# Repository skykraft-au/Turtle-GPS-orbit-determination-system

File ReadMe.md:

# Overview
The Turtle GPS is an open-source, cost-effective, low-power, and low-weight solution to orbit determination. The device resolves the issues faced by standard tracking methods such as radar while democratising space by making tracking cooperative and community-based. The device satisfies CoCom regulations by being post-processed and non-continuous; instead, it beacons GPS data over LoRa packets at specified intervals.

The device is highly configurable through the FPGA Verilog code; see the configuration section below for more information.

Further development on the device is needed; the community is welcome to contribute to this. Information on directions for this development can be found in the Todo section below.

[!WARNING] Turtle GPS v2.0 contains known hardware issues in the flash programming and power supply circuitry which prevent correct operation in the default configuration. These issues are corrected in Turtle GPS v2.1. See GPS v2.0/KNOWN_ISSUES.md for more information. 

# Usage of the Device
## QuickStart Guide for Testing
Once the PCB is fully assembled, the HF MMCX line can be connected to a passive or active GPS antenna. If it is active, in the case of v2.1, the onboard bias tee can power it, otherwise an external bias tee is required. The Turtle GPS should be connected to a 3.3 V power supply, either a small solar panel, a benchtop power supply, or a Lithium-Ion battery. The output can either be connected to an antenna which transmits to a LoRa receiver or directly connected to the receiver with a coaxial cable and a 3 dB attenuator. The LoRa receiver could be setup with a module like the SX1278 RA-02, connected to a microcontroller configured to receive the data packets.

If the Flash has not been programmed, the JTAG header should be connected to a computer over a digilent JTAG-HS3 programming cable or similar. Then, Vivado should be used to compile a bitstream in the relevant project found in this repository. A memory config file using QSPI should be created in Vivado, from this bitstream before being used to write the Flash memory over the JTAG, again with Vivado.

Once programmed, upon being powered the Turtle GPS will begin receiving and transmitting packets of data, following a pseudo-random delay for the first cycle. This delay was implemented to prevent continuous transmission on a tumbling satellite. The packets received over LoRa should be processed with a computer as they are essentially just IQ data from the GPS signal, not processed position or time data.

## Configuration of the Device
By default, the packets transmitted over LoRa are 512 bits wide and include a unique, user-defined satellite ID Code, packet index, user-defined bits, and the actual data.
| Number of Bits | Bit Locations | Purpose |
| -------------- | ------------- | ------- |
| 24 | \[511:488\] | Satellite ID Code |
| 12 | \[487:476\] | Packet Index |
| 28 | \[475:448\] | User-defined bits |
| 448 | \[447:0\] | GPS IQ Data |

The user-defined bits can be configured by changing the value of the respective register in the Verilog code. The configuration of the MAX2771 GNSS Receiver and the LoRa SX1276 can be changed by adjusting the values of their respective configuration registers in the MAX_Driver and LORA_Driver Verilog modules, respectively.

The total transmission size, as well as the sample size and whether samples are continuous or not, can all be configured through the value of the GPS_Config register in the GPS_Top Verilog module. Comments are included in the code to assist users with this.

# Changelog
## Most Recent Version (Turtle GPS v2.1)
- Fixes including 10 kOhm pull-up resistors on Flash Pins, lowered pull up resistance to 1 kOhm on mode pin pullup to prevent metastable behaviour on boot, boost converter swapped to MAX8575, done pin pulled up instead of down, and swapped the power supply diode to B130-13-F for higher current capability.
- Swapped LDOs in the power supply for availability, and lower supply noise.
- Made MMCX connectors side mounted instead of front mounted.
- Swapped power header for the M80-8420245 side-mounted Harwin connector.
- Added an L1 SAW Filter to the RF path around the MAX2771 digitiser.
- Updated LoRa RF path to handle frequencies between 400 and 440 MHz.
- Added a 3.3 V Bias Tee to the GNSS RF input path to allow for an active antenna to be directly connected.
- Moved bulk capacitors to the front of the board allowing direct mounting of the PCB to a satellite chassis with a thin (~0.3 mm) thermally conductive layer.
- Changed Flash to S25FL128LAGMFI010 due to part availability.
- Changed LoRa TCXO to TX21-M010S-32.000-X-R due to part avilability.
- Organised KiCAD Schematic into five distinct sections and added 3D models to components.
- Swapped LoRa clock enable voltage divider for a single pull-up resistor.
- Added voltage divider to the relay in the RF path to better match datasheet requirements.
- Reworked trace length matching for the JTAG, and the Flash memory.
- Updated version number and date.

## Note regarding the Turtle GPS v2.0
The Turtle GPS v2.0 does not work by default, as there are issues regarding the flash and power supply components on the board; these issues are resolved in version 2.1.

# Todo
- Update code to default the LoRa frequency to 401 MHz to 403 MHz and cascade the FIR (or implement a CIC) to allow for a sharper cutoff to be attained with the limited FPGA resources.
- Program LoRa receiving capabilities into the FPGA to allow for remote shutdown with a unique user-defined code.
- Optimise size, weight, and performance of the device
- Test in orbit
- Set up a public website for uploading and processing of data
- Add satellite ID code generator and logger to the website

# Licensing

This repository contains material under multiple licenses.

The Turtle GPS was conceived of by Craig Benson and implemented by Dino Colling as part of work conducted for, and licenced by, Skykraft Pty Ltd.

Copyright © Skykraft Pty Ltd. All rights are licensed as described below.

## Hardware

The hardware design files are licensed under CERN-OHL-P v2.

This includes:
- GPS v2.0/KiCad PCB/
- GPS v2.1/KiCad PCB/

## HDL and Software

The HDL and software source code are licensed under the MIT License.

This includes:
- GPS v2.0/Software and HDL/
- GPS v2.1/Software and HDL/

## Documentation

Documentation, diagrams, and images are licensed under
Creative Commons Attribution 4.0 International (CC BY 4.0).

This includes:
- GPS v2.0/BoM/
- GPS v2.1/BoM/

A copy of each license is available in the licenses/ directory.

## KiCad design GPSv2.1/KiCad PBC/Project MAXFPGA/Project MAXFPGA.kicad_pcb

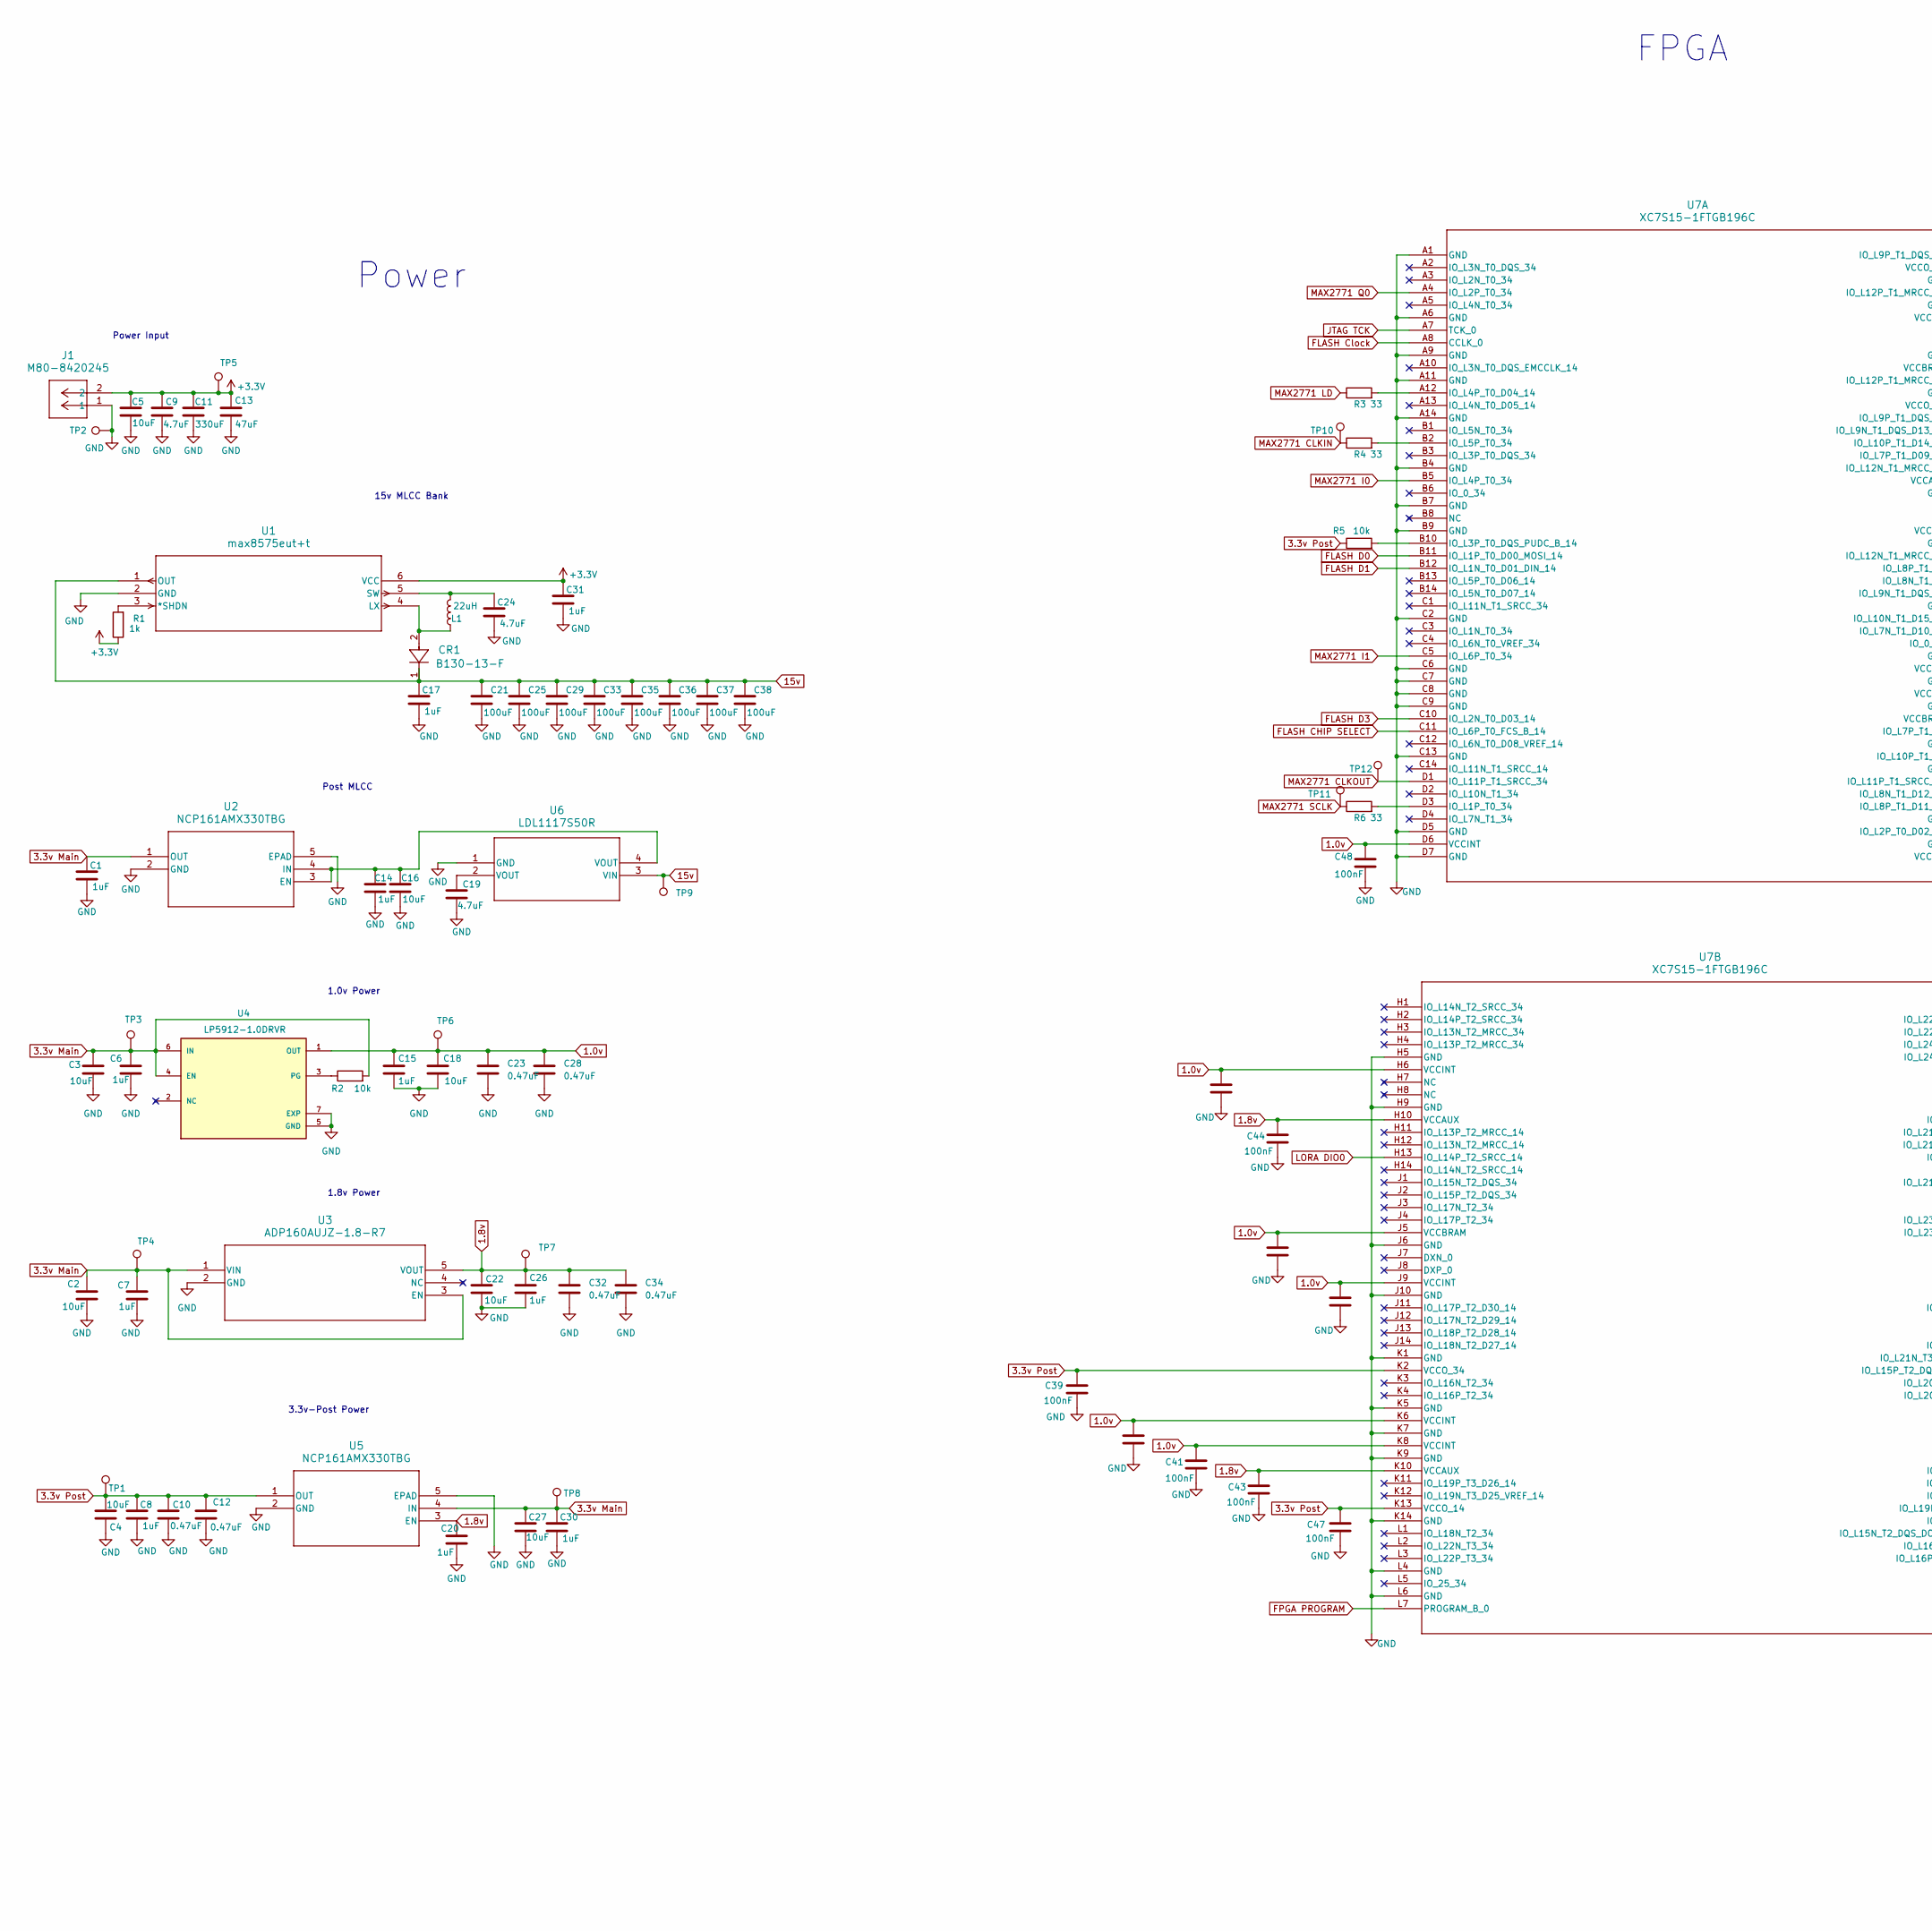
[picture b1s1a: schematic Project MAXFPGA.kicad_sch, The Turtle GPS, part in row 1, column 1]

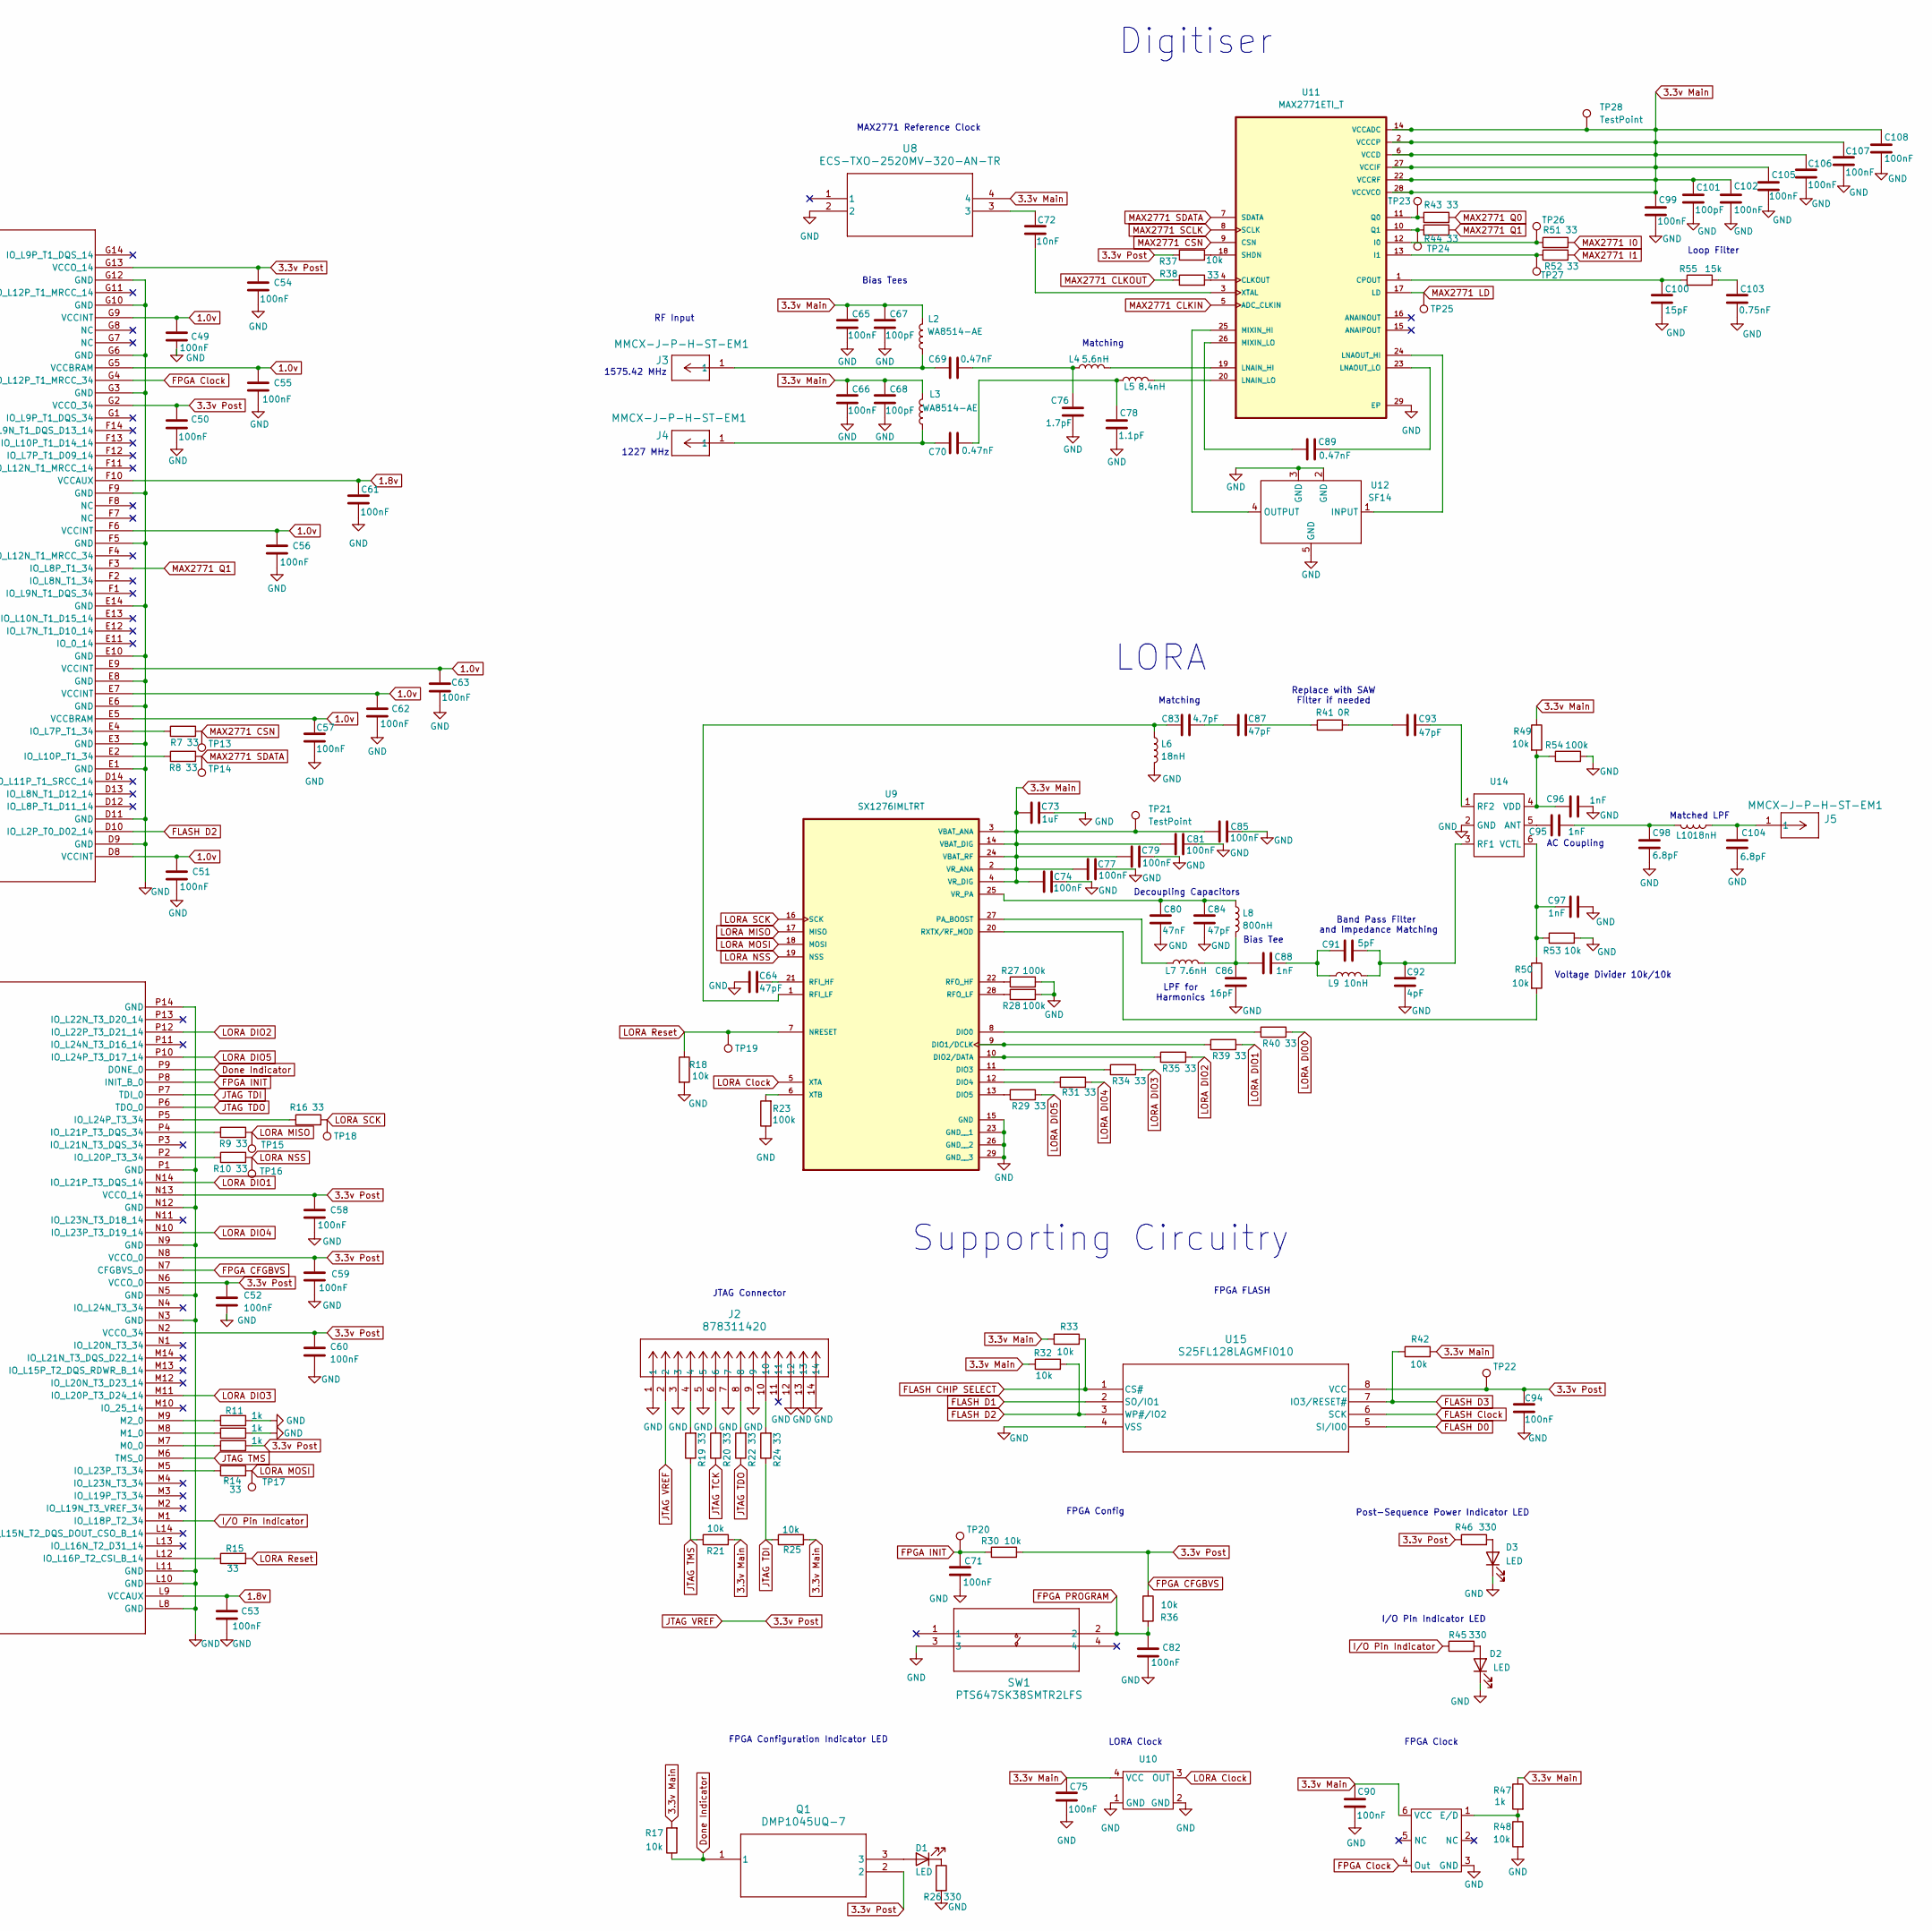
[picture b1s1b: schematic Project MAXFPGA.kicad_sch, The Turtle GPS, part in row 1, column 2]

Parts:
C1, C6, C7, C8, C14, C15, C17, C20, C26, C30, C31, C73: 1uF; C_0402_1005Metric
C2, C3, C4, C5, C16, C18, C22, C27: 10uF; C_0402_1005Metric
C9, C19: 4.7uF; C_0402_1005Metric
C10, C12, C23, C28, C32, C34: 0.47uF; C_0402_1005Metric
C11: 330uF; C_1210_3225Metric
C13: 47uF; C_1206_3216Metric
C21, C25, C29, C33, C35, C36, C37, C38: 100uF; C_1210_3225Metric
C24: 4.7uF; C_0603_1608Metric
C39, C40, C41, C42, C43, C44, C45, C46, C47, C48, C49, C50, C51, C52, C53, C54, C55, C56, C57, C58, C59, C60, C61, C62, C63, C71, C82: 100nF; CAPC0603X33N
C64, C84, C87, C93: 47pF; C_0402_1005Metric
C65, C66, C74, C75, C77, C79, C81, C85, C90, C94, C99, C102, C105, C106, C107, C108: 100nF; C_0402_1005Metric
C67, C68, C101: 100pF; C_0402_1005Metric
C69, C70, C89: 0.47nF; C_0201_0603Metric
C72: 10nF; C_0402_1005Metric
C76: 1.7pF; C_0402_1005Metric
C78: 1.1pF; C_0402_1005Metric
C80: 47nF; C_0402_1005Metric
C83: 4.7pF; C_0402_1005Metric
C86: 16pF; C_0402_1005Metric
C88, C95: 1nF; C_0201_0603Metric
C91: 5pF; C_0402_1005Metric
C92: 4pF; C_0402_1005Metric
C96, C97: 1nF; C_0402_1005Metric
C98, C104: 6.8pF; C_0402_1005Metric
C100: 15pF; CAPC17595_87N_KEM
C103: 0.75nF; C_0402_1005Metric
CR1: B130-13-F; D_SMA
D1, D2, D3: LED; LED_SML-D12U1WT86
J1: M80-8420245; CONN_M80-84202_HRW
J2: 878311420; JTAG_Conn
J3, J4, J5: MMCX-J-P-H-ST-EM1; CONN_MMCX-J-P-H-ST-EM1_SAI
L1: 22uH; L_0805_2012Metric
L2, L3: WA8514-AE; RF_Choke
L4: 5.6nH; INDC1006X60N
L5: 8.4nH; INDC1006X60N
L6, L10: 18nH; INDC1006X60N
L7: 7.6nH; INDC1006X60N
L8: 800nH; INDC1006X60N
L9: 10nH; INDC1006X60N
Q1: DMP1045UQ-7; DONE_FET
R1, R11, R12, R13, R47: 1k; RESC1005X40N
R2, R5, R17, R18, R21, R25, R30, R32, R33, R36, R37, R42, R48, R49, R50, R53: 10k; RESC1005X40N
R3, R4, R6, R7, R8, R9, R10, R14, R15, R16, R19, R20, R22, R24, R29, R31, R34, R35, R38, R39, R40, R43, R44, R51, R52: 33; RESC1005X40N
R23, R27, R28, R54: 100k; RESC1005X40N
R26, R45, R46: 330; RESC1005X40N
R41: 0R; RESC1005X40N
R55: 15k; RES_ERA2AEB153X
SW1: PTS647SK38SMTR2LFS; PTS647SK38SMTR2LFS_CNK
TP1, TP2, TP3, TP4, TP5, TP6, TP7, TP8, TP9, TP10, TP11, TP12, TP13, TP14, TP15, TP16, TP17, TP18, TP19, TP20, TP21, TP22, TP23, TP24, TP25, TP26, TP27, TP28: TestPoint; TestPoint_Pad_1.0x1.0mm
U1: max8575eut+t; Boost
U2, U5: NCP161AMX330TBG; XDFN4_711AJ_ONS_OSI
U3: ADP160AUJZ-1.8-R7; 1.8V_REG
U4: LP5912-1.0DRVR; SON65P200X200X80-7N; PARTREV D
U6: LDL1117S50R; SOT223_STM-M
U7: XC7S15-1FTGB196C; FTGB196_AMD
U8: ECS-TXO-2520MV-320-AN-TR; SMD04_XTAL_2P5X2_ECS
U9: SX1276IMLTRT; QFN65P600X600X100-29N; PARTREV 5
U10: LoRa_Clock_32MHz
U11: MAX2771ETI_T; QFN50P500X500X80-29N
U12: SF14; Untitled
U13: FPGA_Clock_100MHz
U14: ASWD-S2-000
U15: S25FL128LAGMFI010; SOIC8_S25FL_CYP-M

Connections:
1.0v: C15.1, C18.1, C23.1, C28.1, C40.1, C41.1, C42.1, C45.1, C46.1, C48.2, C49.1, C51.1, C55.1, C56.1, C57.1, C62.1, C63.2, TP6.1 (1_1), U4.1 (OUT), U7.D6 (VCCINT), U7.D8 (VCCINT), U7.E5 (VCCBRAM), U7.E7 (VCCINT), U7.E9 (VCCINT), U7.F6 (VCCINT), U7.G5 (VCCBRAM), U7.G9 (VCCINT), U7.H6 (VCCINT), U7.J5 (VCCBRAM), U7.J9 (VCCINT), U7.K6 (VCCINT), U7.K8 (VCCINT)
1.8v: C20.1, C22.2, C26.2, C32.1, C34.1, C43.2, C44.1, C53.2, C61.2, TP7.1 (1_1), U3.5 (VOUT), U5.3 (EN), U7.F10 (VCCAUX), U7.H10 (VCCAUX), U7.K10 (VCCAUX), U7.L9 (VCCAUX)
3.3v Main: C1.1, C2.1, C3.1, C6.1, C7.1, C27.1, C30.1, C65.2, C66.2, C67.2, C68.2, C73.1, C74.1, C75.1, C77.1, C79.1, C81.1, C85.1, C90.1, C99.1, C101.1, C102.1, C105.1, C106.1, C107.1, C108.1, L2.2, L3.2, R2.2, R17.2, R21.2, R25.2, R32.1, R33.1, R42.2, R47.1, R49.1, TP3.1 (1_1), TP4.1 (1_1), TP8.1 (1_1), TP21.1 (1_1), TP28.1 (1_1), U2.1 (OUT), U3.1 (VIN), U3.3 (EN), U4.4 (EN), U4.6 (IN), U5.4 (IN), U8.4, U9.2 (VR_ANA), U9.3 (VBAT_ANA), U9.4 (VR_DIG), U9.14 (VBAT_DIG), U9.24 (VBAT_RF), U10.4 (VCC), U11.2 (VCCCP), U11.6 (VCCD), U11.14 (VCCADC), U11.22 (VCCRF), U11.27 (VCCIF), U11.28 (VCCVCO), U13.6 (VCC)
3.3v Post: C4.1, C8.1, C10.1, C12.1, C39.1, C47.1, C50.1, C52.1, C54.1, C58.1, C59.1, C60.1, C94.1, J2.2, Q1.2, R5.1, R13.2, R30.2, R36.1, R37.1, R46.1, TP1.1 (1_1), TP22.1 (1_1), U5.1 (OUT), U7.G2 (VCCO_34), U7.G13 (VCCO_14), U7.K2 (VCCO_34), U7.K13 (VCCO_14), U7.N2 (VCCO_34), U7.N6 (VCCO_0), U7.N7 (CFGBVS_0), U7.N8 (VCCO_0), U7.N13 (VCCO_14), U15.8 (VCC); also elsewhere on the board
15v: C17.1, C21.2, C25.2, C29.2, C33.2, C35.2, C36.2, C37.2, C38.2, CR1.1, TP9.1 (1_1), U1.1 (OUT), U6.3 (VIN)
+3.3V: C5.2, C9.2, C11.2, C13.2, C31.1, J1.2, R1.1, TP5.1 (1_1), U1.6 (VCC); also elsewhere on the board
Done Indicator: Q1.1, R17.1, U7.P9 (DONE_0)
FLASH CHIP SELECT: R33.2, U7.C11 (IO_L6P_T0_FCS_B_14), U15.1 (CS#); also elsewhere on the board
FLASH Clock: U7.A8 (CCLK_0), U15.6 (SCK); also elsewhere on the board
FLASH D0: U7.B11 (IO_L1P_T0_D00_MOSI_14), U15.5 (SI/IO0); also elsewhere on the board
FLASH D1: U7.B12 (IO_L1N_T0_D01_DIN_14), U15.2 (SO/IO1); also elsewhere on the board
FLASH D2: R32.2, U7.D10 (IO_L2P_T0_D02_14), U15.3 (WP#/IO2); also elsewhere on the board
FLASH D3: R42.1, U7.C10 (IO_L2N_T0_D03_14), U15.7 (IO3/RESET#); also elsewhere on the board
FPGA Clock: U7.G4 (IO_L12P_T1_MRCC_34), U13.4 (Out)
FPGA INIT: C71.1, R30.1, TP20.1 (1_1), U7.P8 (INIT_B_0)
FPGA PROGRAM: C82.1, R36.2, SW1.2, U7.L7 (PROGRAM_B_0); also elsewhere on the board
GND: C1.2, C2.2, C3.2, C4.2, C5.1, C6.2, C7.2, C8.2, C9.1, C10.2, C11.1, C12.2, C13.1, C14.2, C15.2, C16.2, C17.2, C18.2, C19.2, C20.2, C21.1, C22.1, C23.2, C24.2, C25.1, C26.1, C27.2, C28.2, C29.1, C30.2, C31.2, C32.2, C33.1, C34.2, C35.1, C36.1, C37.1, C38.1, C39.2, C40.2, C41.2, C42.2, C43.1, C44.2, C45.2, C46.2, C47.2, C48.1, C49.2, C50.2, C51.2, C52.2, C53.1, C54.2, C55.2, C56.2, C57.2, C58.2, C59.2, C60.2, C61.1, C62.2, C63.1, C64.1, C65.1, C66.1, C67.1, C68.1, C71.2, C73.2, C74.2, C75.2, C76.2, C77.2, C78.2, C79.2, C80.2, C81.2, C82.2, C84.2, C85.2, C86.2, C90.2, C92.2, C94.2, C96.2, C97.2, C98.2, C99.2, C100.2, C101.2, C102.2, C103.2, C104.2, C105.2, C106.2, C107.2, C108.2, D2.1 (K), D2.K, D3.1 (K), D3.K, J1.1, J2.1, J2.3, J2.5, J2.7, J2.9, J2.12, J2.13, J2.14, L6.2, R11.2, R12.2, R18.2, R23.1, R26.2, R27.2, R28.2, R48.2, R53.2, R54.2, SW1.3, TP2.1 (1_1), U1.2 (GND), U2.2 (GND), U2.5 (EPAD), U3.2 (GND), U4.5 (GND), U4.7 (EXP), U5.2 (GND), U5.5 (EPAD), U6.1 (GND), U7.A1 (GND), U7.A6 (GND), U7.A9 (GND), U7.A11 (GND), U7.A14 (GND), U7.B4 (GND), U7.B7 (GND), U7.B9 (GND), U7.C2 (GND), U7.C6 (GND), U7.C7 (GND), U7.C8 (GND), U7.C9 (GND), U7.C13 (GND), U7.D5 (GND), U7.D7 (GND), U7.D9 (GND), U7.D11 (GND), U7.E1 (GND), U7.E3 (GND), U7.E6 (GND), U7.E8 (GND), U7.E10 (GND), U7.E14 (GND), U7.F5 (GND), U7.F9 (GND), U7.G3 (GND), U7.G6 (GND), U7.G10 (GND), U7.G12 (GND), U7.H5 (GND), U7.H9 (GND), U7.J6 (GND), U7.J10 (GND), U7.K1 (GND), U7.K5 (GND), U7.K7 (GND), U7.K9 (GND), U7.K14 (GND), U7.L4 (GND), U7.L6 (GND), U7.L8 (GND), U7.L10 (GND), U7.L11 (GND), U7.N3 (GND), U7.N5 (GND), U7.N9 (GND), U7.N12 (GND), U7.P1 (GND), U7.P14 (GND), U8.2, U9.15 (GND), U9.23 (GND__1), U9.26 (GND__2), U9.29 (GND__3), U10.1 (GND), U10.2 (GND), U11.29 (EP), U12.2 (GND), U12.3 (GND), U12.5 (GND), U13.3 (GND), U14.2 (GND), U15.4 (VSS); also elsewhere on the board
I/O Pin Indicator: R45.1, U7.M1 (IO_L18P_T2_34)
JTAG TCK: R20.1, U7.A7 (TCK_0)
JTAG TDI: R24.1, R25.1, U7.P7 (TDI_0)
JTAG TDO: R22.1, U7.P6 (TDO_0)
JTAG TMS: R19.1, R21.1, U7.M6 (TMS_0)
LORA Clock: U9.5 (XTA), U10.3 (OUT)
LORA DIO0: R40.2, U7.H13 (IO_L14P_T2_SRCC_14)
LORA DIO1: R39.2, U7.N14 (IO_L21P_T3_DQS_14)
LORA DIO2: R35.2, U7.P12 (IO_L22P_T3_D21_14)
LORA DIO3: R34.2, U7.M11 (IO_L20P_T3_D24_14)
LORA DIO4: R31.2, U7.N10 (IO_L23P_T3_D19_14)
LORA DIO5: R29.2, U7.P10 (IO_L24P_T3_D17_14)
LORA MISO: R9.2, TP15.1 (1_1), U9.17 (MISO)
LORA MOSI: R14.2, TP17.1 (1_1), U9.18 (MOSI)
LORA NSS: R10.2, TP16.1 (1_1), U9.19 (NSS)
LORA Reset: R15.2, R18.1, TP19.1 (1_1), U9.7 (NRESET)
LORA SCK: R16.2, TP18.1 (1_1), U9.16 (SCK)
MAX2771 CLKIN: R4.1, TP10.1 (1_1), U11.5 (ADC_CLKIN)
MAX2771 CLKOUT: R38.1, TP12.1 (1_1), U7.D1 (IO_L11P_T1_SRCC_34)
MAX2771 CSN: R7.2, TP13.1 (1_1), U11.9 (CSN)
MAX2771 I0: R51.2, U7.B5 (IO_L4P_T0_34)
MAX2771 I1: R52.2, U7.C5 (IO_L6P_T0_34)
MAX2771 LD: R3.1, TP25.1 (1_1), U11.17 (LD)
MAX2771 Q0: R43.2, U7.A4 (IO_L2P_T0_34)
MAX2771 Q1: R44.2, U7.F3 (IO_L8P_T1_34)
MAX2771 SCLK: R6.1, TP11.1 (1_1), U11.8 (SCLK)
MAX2771 SDATA: R8.2, TP14.1 (1_1), U11.7 (SDATA)
unnamed: C19.1, U6.2 (VOUT)
unnamed 45: C69.1, J3.1, L2.1; also elsewhere on the board
unnamed: C69.2, C76.1, L4.1
unnamed 47: C70.1, J4.1, L3.1; also elsewhere on the board
unnamed: C70.2, C78.1, L5.1
unnamed: C72.2, U8.3
unnamed: C83.2, C87.1
unnamed: C86.1, C88.1, L7.2, L8.2
unnamed: C87.2, R41.1
unnamed: C88.2, C91.1, L9.1
unnamed: C93.1, R41.2
unnamed: C95.2, C98.1, L10.2
unnamed: C103.1, R55.2
unnamed 57: C104.1, J5.1, L10.1; also elsewhere on the board
unnamed: D1.2 (A), D1.A, Q1.3
unnamed: D1.1 (K), D1.K, R26.1
unnamed: D2.2 (A), D2.A, R45.2
unnamed: D3.2 (A), D3.A, R46.2
unnamed 62: J2.4, R19.2; also elsewhere on the board
unnamed 63: J2.6, R20.2; also elsewhere on the board
unnamed 64: J2.8, R22.2; also elsewhere on the board
unnamed 65: J2.10, R24.2; also elsewhere on the board
unnamed: R1.2, U1.3 (*SHDN)
unnamed: CR1.2, L1.1, U1.4 (LX)
unnamed: C24.1, L1.2, U1.5 (SW)
unnamed: C14.1, C16.1, U2.3 (EN), U2.4 (IN), U6.4 (VOUT)
unnamed: R2.1, U4.3 (PG)
unnamed: R6.2, U7.D3 (IO_L1P_T0_34)
unnamed: R5.2, U7.B10 (IO_L3P_T0_DQS_PUDC_B_14)
unnamed: R3.2, U7.A12 (IO_L4P_T0_D04_14)
unnamed: R4.2, U7.B2 (IO_L5P_T0_34)
unnamed: R7.1, U7.E4 (IO_L7P_T1_34)
unnamed: R8.1, U7.E2 (IO_L10P_T1_34)
unnamed: R15.1, U7.L12 (IO_L16P_T2_CSI_B_14)
unnamed: R10.1, U7.P2 (IO_L20P_T3_34)
unnamed: R9.1, U7.P4 (IO_L21P_T3_DQS_34)
unnamed: R14.1, U7.M5 (IO_L23P_T3_34)
unnamed: R16.1, U7.P5 (IO_L24P_T3_34)
unnamed: R13.1, U7.M7 (M0_0)
unnamed: R12.1, U7.M8 (M1_0)
unnamed: R11.1, U7.M9 (M2_0)
unnamed: R40.1, U9.8 (DIO0)
unnamed: R39.1, U9.9 (DIO1/DCLK)
unnamed: R35.1, U9.10 (DIO2/DATA)
unnamed: R34.1, U9.11 (DIO3)
unnamed: R31.1, U9.12 (DIO4)
unnamed: R29.1, U9.13 (DIO5)
unnamed: L7.1, U9.27 (PA_BOOST)
unnamed: C64.2, U9.21 (RFI_HF)
unnamed: C83.1, L6.1, U9.1 (RFI_LF)
unnamed: R27.1, U9.22 (RFO_HF)
unnamed: R28.1, U9.28 (RFO_LF)
unnamed: R50.2, U9.20 (RXTX/RF_MOD)
unnamed: C80.1, C84.1, L8.1, U9.25 (VR_PA)
unnamed: R23.2, U9.6 (XTB)
unnamed: R38.2, U11.4 (CLKOUT)
unnamed: C100.1, R55.1, U11.1 (CPOUT)
unnamed: R51.1, TP26.1 (1_1), U11.12 (I0)
unnamed: R52.1, TP27.1 (1_1), U11.13 (I1)
unnamed: L4.2, U11.19 (LNAIN_HI)
unnamed: L5.2, U11.20 (LNAIN_LO)
unnamed: U11.24 (LNAOUT_HI), U12.1 (INPUT)
unnamed: C89.2, U11.23 (LNAOUT_LO)
unnamed: U11.25 (MIXIN_HI), U12.4 (OUTPUT)
unnamed: C89.1, U11.26 (MIXIN_LO)
unnamed: R43.1, TP23.1 (1_1), U11.11 (Q0)
unnamed: R44.1, TP24.1 (1_1), U11.10 (Q1)
unnamed: R37.2, U11.18 (SHDN)
unnamed: C72.1, U11.3 (XTAL)
unnamed: R47.2, R48.1, U13.1 (E/D)
unnamed: C95.1, U14.5 (ANT)
unnamed: C91.2, C92.1, L9.2, U14.3 (RF1)
unnamed: C93.2, U14.1 (RF2)
unnamed: C97.1, R50.1, R53.1, U14.6 (VCTL)
unnamed: C96.1, R49.2, R54.1, U14.4 (VDD)

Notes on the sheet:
1.0v Power
Post-Sequence Power Indicator LED
FPGA FLASH
FPGA Config
Matched LPF
Power Input
Post MLCC
Digitiser
LORA Clock
Band Pass Filter and Impedance Matching
15v MLCC Bank
1575.42 MHz
FPGA
Replace with SAW Filter if needed
FPGA Clock
1.8v Power
I/O Pin Indicator LED
Bias Tees
RF Input
LPF for Harmonics
FPGA Configuration Indicator LED
Matching
Matching
AC Coupling
Voltage Divider 10k/10k
Supporting Circuitry
Decoupling Capacitors
3.3v-Post Power
1227 MHz
Power
JTAG Connector
Loop Filter
MAX2771 Reference Clock
Bias Tee
LORA

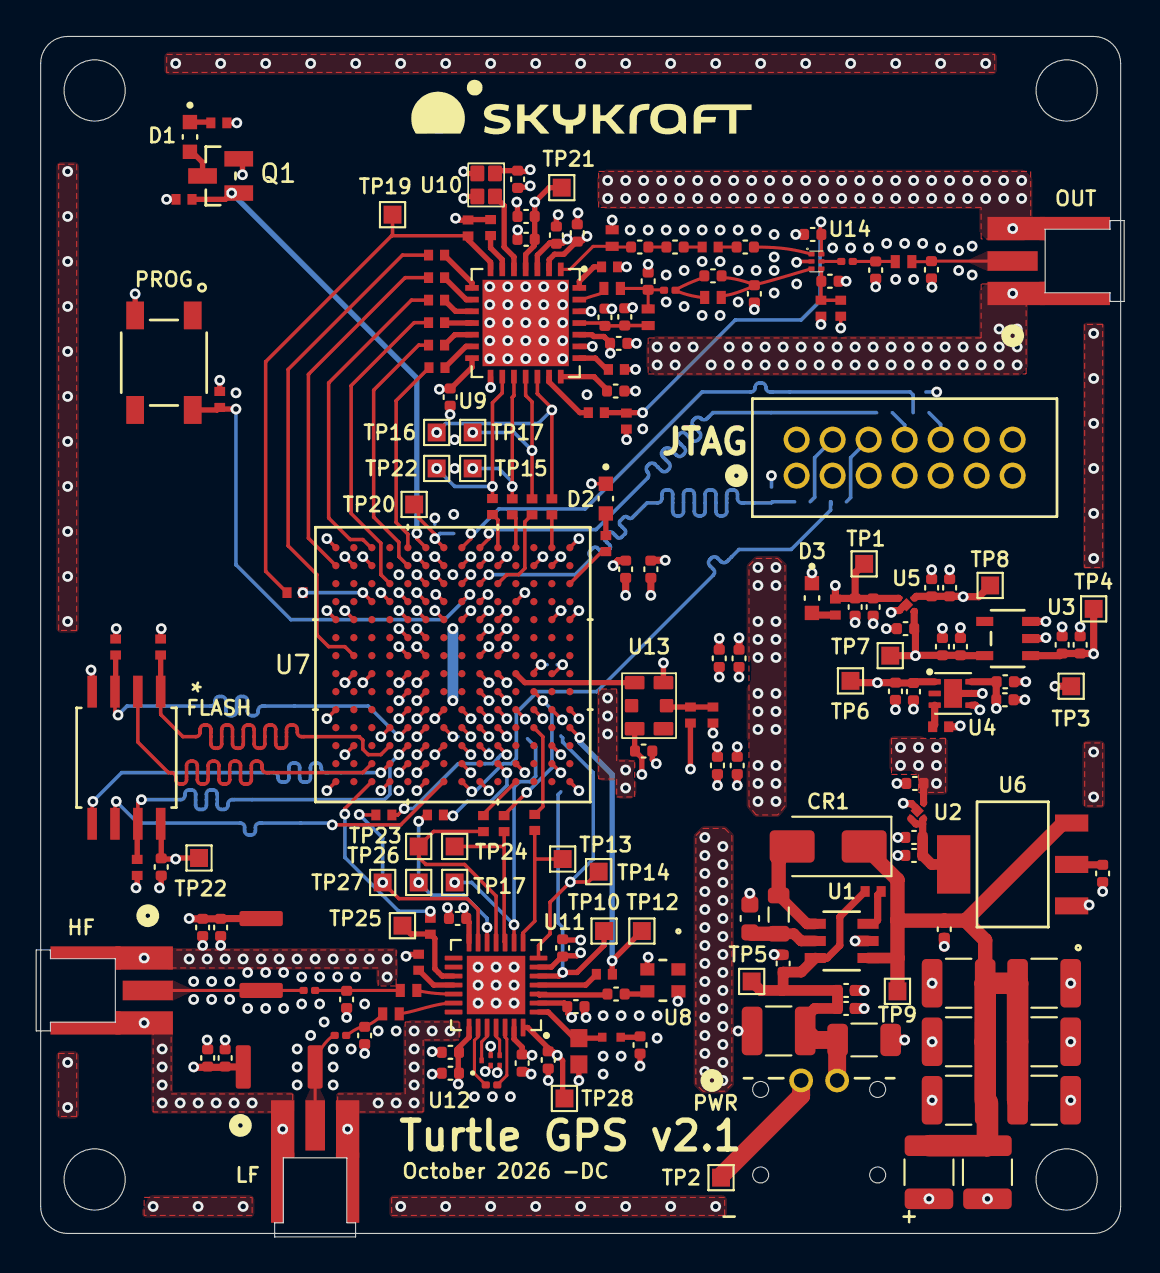
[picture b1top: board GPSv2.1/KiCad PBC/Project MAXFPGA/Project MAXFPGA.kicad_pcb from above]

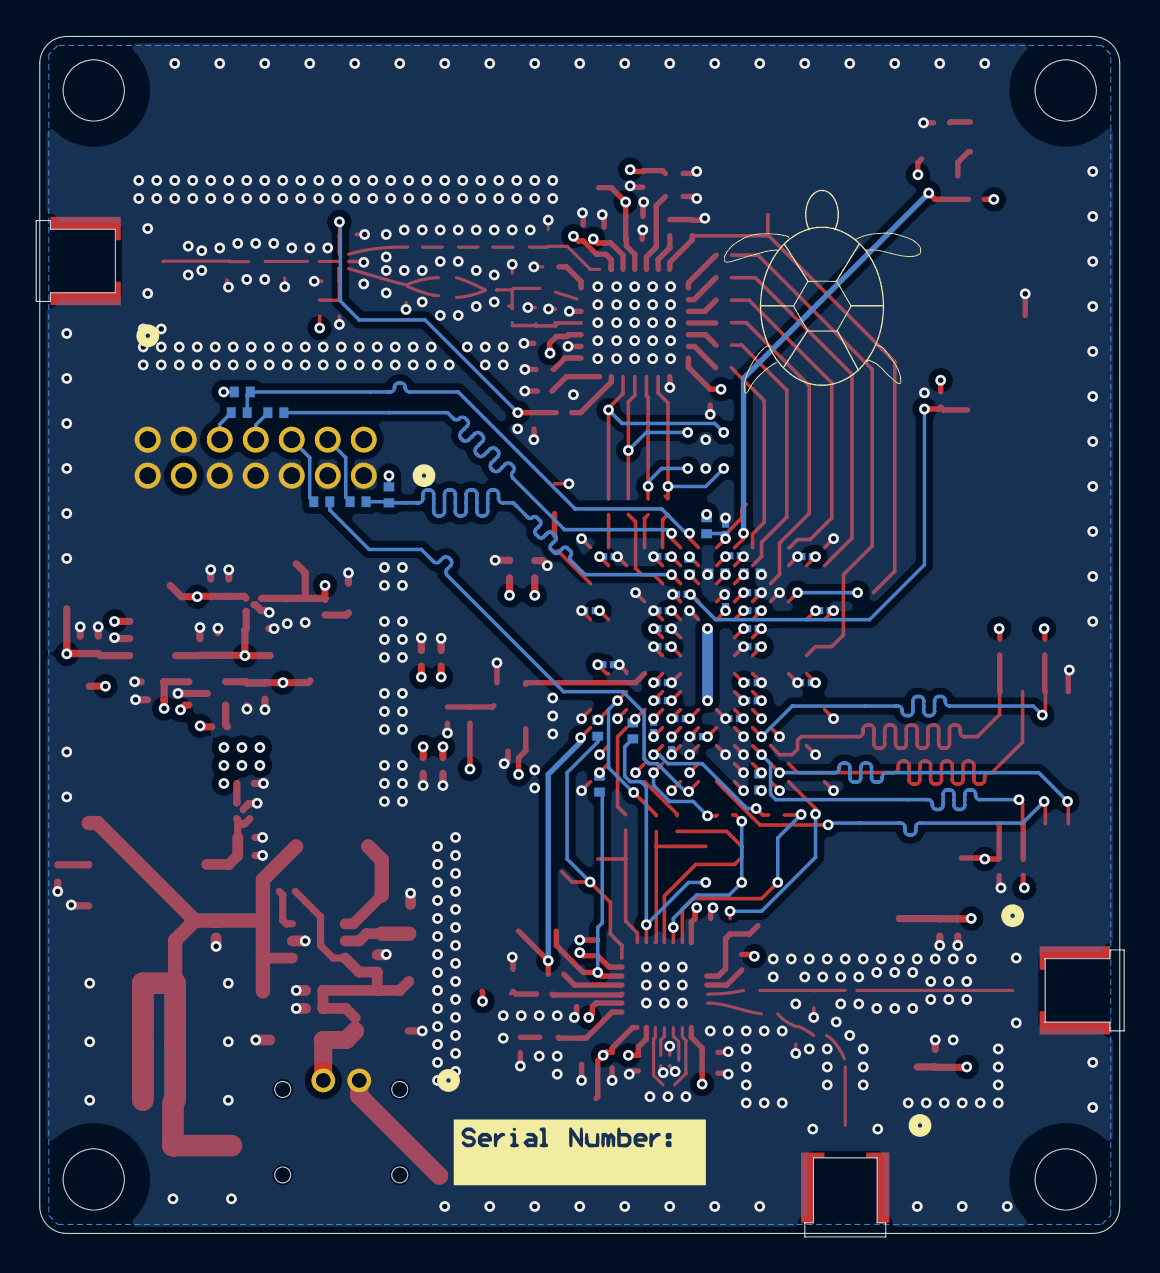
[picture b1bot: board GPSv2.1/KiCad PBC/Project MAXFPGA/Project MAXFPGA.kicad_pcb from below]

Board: 4 copper layers, 60.0 x 66.5 mm, 227 parts (41 on the bottom side), 119 nets.

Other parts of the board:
FLASH: S25FL128LAGMFI010; SOIC8_S25FL_CYP-M
HF: MMCX-J-P-H-ST-EM1; CONN_MMCX-J-P-H-ST-EM1_SAI
JTAG: 878311420; JTAG_Conn
LF: MMCX-J-P-H-ST-EM1; CONN_MMCX-J-P-H-ST-EM1_SAI
OUT: MMCX-J-P-H-ST-EM1; CONN_MMCX-J-P-H-ST-EM1_SAI
PROG: PTS647SK38SMTR2LFS; PTS647SK38SMTR2LFS_CNK
PWR: M80-8420245; CONN_M80-84202_HRW

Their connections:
3.3v Post: FLASH.8 (VCC), JTAG.2; also elsewhere on the board
+3.3V: PWR.2; also elsewhere on the board
FLASH CHIP SELECT: FLASH.1 (CS#); also elsewhere on the board
FLASH Clock: FLASH.6 (SCK); also elsewhere on the board
FLASH D0: FLASH.5 (SI/IO0); also elsewhere on the board
FLASH D1: FLASH.2 (SO/IO1); also elsewhere on the board
FLASH D2: FLASH.3 (WP#/IO2); also elsewhere on the board
FLASH D3: FLASH.7 (IO3/RESET#); also elsewhere on the board
FPGA PROGRAM: PROG.2; also elsewhere on the board
GND: FLASH.4 (VSS), HF.2, HF.3, JTAG.1, JTAG.3, JTAG.5, JTAG.7, JTAG.9, JTAG.12, JTAG.13, JTAG.14, LF.2, LF.3, OUT.2, OUT.3, PROG.3, PWR.1; also elsewhere on the board
unnamed 45: HF.1 (1_1); also elsewhere on the board
unnamed 47: LF.1 (1_1); also elsewhere on the board
unnamed 57: OUT.1 (1_1); also elsewhere on the board
unnamed 62: JTAG.4; also elsewhere on the board
unnamed 63: JTAG.6; also elsewhere on the board
unnamed 64: JTAG.8; also elsewhere on the board
unnamed 65: JTAG.10; also elsewhere on the board
